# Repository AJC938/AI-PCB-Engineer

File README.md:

# AI-PCB-Engineer

An open-source electronics project delivering a protected sensor interface and peripheral power board for an **external ESP32 DevKit**.

> **Featured hardware:** Sensor Interface & Power Management Board for ESP32 · Rev A · V1.0.0
> CAD visualization only — **not fabricated or physically tested**.

## What is this PCB?

The board organizes power and signal connections between an ESP32 DevKit and compatible peripherals. It provides protected 5 V distribution, a regulated 3.3 V peripheral rail, conditioned sensor signals, and I²C, UART, and GPIO headers. The ESP32 is a separate development board and is powered through its own USB connection.

## Problem and solution

ESP32 GPIO uses 3.3 V logic and is not 5 V tolerant. Some 5 V ultrasonic modules can return a 5 V ECHO signal, which may exceed an ESP32 input's limits. Loose jumper-wire circuits also make power and signal wiring easier to get wrong.

This board provides a documented connector layout and dedicated signal conditioning: an SN74LVC1T45 translates ESP32 TRIG to the sensor's 5 V logic side, while an SN74LVC1G17 conditions ECHO for the ESP32. It also supplies protected 5 V and regulated 3.3 V peripheral power. Compatibility depends on the module's actual pinout and electrical characteristics; follow the [connector guide](docs/pinout/CONNECTION_GUIDE.md).

**Power regulation** creates a regulated supply rail. **Signal conditioning** adapts signal levels for compatible communication. They are separate circuits on this board.

## How it works

```mermaid
flowchart LR
  IN[5 V DC input] --> EF[TPS26600 eFuse] --> R5[Protected +5V_P]
  R5 --> LDO[TLV1117LV33] --> R3[+3V3_P peripheral rail]
  R5 --> USV[Ultrasonic VCC]
  ESP[External ESP32 DevKit<br/>powered separately by USB] --> IF[ESP32 signal interface]
  IF -->|TRIG, 3.3 V| TX[SN74LVC1T45]
  TX -->|TRIG, 5 V| US[Ultrasonic connector]
  US -->|ECHO, up to 5 V| RX[SN74LVC1G17]
  RX -->|conditioned ECHO| IF
  IF --> COM[I2C · UART · GPIO connectors]
  R3 -->|J5/J6; J4 via JP1| PER[Peripheral power]
  ESP ---|GND reference| US
```

`+3V3_P` powers peripherals. `3V3_ESP` is a separate ESP32 logic reference; the two rails are not connected together. See the [system architecture](docs/system-architecture/BOARD_ARCHITECTURE.md) and [electrical design](docs/electrical-design/ELECTRICAL_DESIGN.md).

## PCB gallery

Captured from the actual V1.0.0 project in KiCad applications. These are GUI screenshots, not command-line exports.

| Full schematic | PCB top layout |
|---|---|
|  |  |

| PCB bottom copper | 3D top view |
|---|---|
|  |  |

| 3D bottom view | Connector details |
|---|---|
|  |  |

[Power management schematic close-up](docs/visual-review/images/screenshots/02-power-management.png) · [All visual-review assets](docs/visual-review/VISUAL_REVIEW.md)

## Key specifications

| Item | Rev A specification |
|---|---|
| Board | 90 × 64 mm; 2 layers; FR-4; 1.6 mm; 1 oz copper |
| Component instances | 44 SMT + 8 THT = 52 |
| Input | Regulated 5 V DC, ±5%; ≥0.7 A recommended supply capacity |
| Peripheral rails | Protected +5V_P; regulated +3V3_P |
| 3.3 V peripheral load | 250 mA maximum, **calculated** at ambient ≤50 °C; not measured |
| Interfaces | ESP32 header, ultrasonic, I²C, UART, general-purpose GPIO |
| Primary protection | TPS26600 eFuse; current limit 0.51–0.69 A per release data |
| Validation | ERC 0; DRC 0 errors / 0 warnings; 0 unconnected; schematic parity 0 |

See [release notes](release/v1.0.0/RELEASE_NOTES_V1.0.0.md) and [digital validation evidence](docs/validation/DIGITAL_VALIDATION.md).

## Main components

- **TPS26600PWPR** — input eFuse with adjustable protection and current management.
- **TLV1117LV33** — regulates protected 5 V to the peripheral 3.3 V rail.
- **SN74LVC1T45** — translates ESP32 TRIG logic to the 5 V sensor side.
- **SN74LVC1G17** — conditions the ECHO input for the ESP32 logic domain.
- **J1–J6** — power input, ESP32, ultrasonic, UART, I²C, and GPIO connections.

[Complete BOM (CSV)](manufacturing/Sensor_Interface_Power_Board/RevA/assembly/Sensor_Interface_Power_Board_RevA_BOM.csv) · [Connector pinout](docs/pinout/CONNECTION_GUIDE.md)

## Downloads

| File | Download |
|---|---|
| KiCad project | [Project file](hardware/kicad/Sensor_Interface_Power_Board/Sensor_Interface_Power_Board.kicad_pro) · [Schematic](hardware/kicad/Sensor_Interface_Power_Board/Sensor_Interface_Power_Board.kicad_sch) · [PCB](hardware/kicad/Sensor_Interface_Power_Board/Sensor_Interface_Power_Board.kicad_pcb) |
| Complete manufacturing package | [ZIP](manufacturing/Sensor_Interface_Power_Board/RevA/packages/Sensor_Interface_PCB_RevA_Complete_Manufacturing.zip) |
| Fabrication package | [ZIP](manufacturing/Sensor_Interface_Power_Board/RevA/packages/Sensor_Interface_PCB_RevA_Fabrication.zip) |
| Assembly package | [ZIP](manufacturing/Sensor_Interface_Power_Board/RevA/packages/Sensor_Interface_PCB_RevA_Assembly.zip) |
| Copper Gerbers | [Top copper](manufacturing/Sensor_Interface_Power_Board/RevA/fabrication/Sensor_Interface_Power_Board-F_Cu.gtl) · [Bottom copper](manufacturing/Sensor_Interface_Power_Board/RevA/fabrication/Sensor_Interface_Power_Board-B_Cu.gbl) |
| Drill files | [Plated](manufacturing/Sensor_Interface_Power_Board/RevA/fabrication/Sensor_Interface_Power_Board-PTH.drl) · [Non-plated](manufacturing/Sensor_Interface_Power_Board/RevA/fabrication/Sensor_Interface_Power_Board-NPTH.drl) |
| Assembly data | [BOM](manufacturing/Sensor_Interface_Power_Board/RevA/assembly/Sensor_Interface_Power_Board_RevA_BOM.csv) · [CPL](manufacturing/Sensor_Interface_Power_Board/RevA/assembly/Sensor_Interface_Power_Board_RevA_CPL.csv) |
| 3D model | [STEP](manufacturing/Sensor_Interface_Power_Board/RevA/3d/Sensor_Interface_Power_Board_RevA.step) |
| Schematic | [PDF](manufacturing/Sensor_Interface_Power_Board/RevA/assembly/Sensor_Interface_Power_Board_RevA_schematic.pdf) |

## How to use

1. Supply the PCB with the specified regulated 5 V input.
2. Power the external ESP32 DevKit separately through its own USB connector.
3. Connect ESP32 signals using the documented interface and pinout.
4. Connect a compatible sensor using its documented connector labels and electrical requirements.
5. Follow the [power and safety requirements](docs/safety/SAFETY_AND_POWER.md), including sequencing rule R-31.

## Manufacturing

Download the [complete manufacturing ZIP](manufacturing/Sensor_Interface_Power_Board/RevA/packages/Sensor_Interface_PCB_RevA_Complete_Manufacturing.zip) or the separate fabrication and assembly packages. Ask a compatible supplier to confirm its capabilities, file requirements, and component sourcing before placing an order. The TPS26600PWPR stock status was uncertain at release; substitutions require written approval. See the [manufacturing guide](manufacturing/Sensor_Interface_Power_Board/RevA/fabrication/FABRICATION_NOTES.md) and [assembly requirements](docs/assembly/FULL_ASSEMBLY_REQUIREMENTS.md).

## Validation and limitations

**DIGITALLY VALIDATED — NOT FABRICATED OR PHYSICALLY TESTED.** ERC/DRC results are digital checks; no thermal, electrical, or functional measurements have been made.

- Reverse-polarity protection has a ground-loop limitation when other earthed equipment shares ground.
- Surge protection has not been demonstrated; do not infer a surge rating.
- The 3.3 V peripheral rail is limited to 250 mA calculated at ambient ≤50 °C.
- Follow power-sequencing rule R-31: power this board before or together with the ESP32.
- Sensor mating pin order has not been verified; check the module's own documentation.
- TPS26600PWPR availability was not confirmed on 2026-11-09.

Details: [physical validation status](docs/validation/PHYSICAL_VALIDATION_STATUS.md), [safety notes](docs/safety/SAFETY_AND_POWER.md), and [release notes](release/v1.0.0/RELEASE_NOTES_V1.0.0.md).

## License

Hardware design files and hardware documentation: [CERN-OHL-P-2.0](LICENSE-HARDWARE). Code: [MIT](LICENSE-CODE). Third-party material remains under its own terms; see [license scope](LICENSE_SCOPE.md) and [third-party notices](THIRD_PARTY_NOTICES.md).

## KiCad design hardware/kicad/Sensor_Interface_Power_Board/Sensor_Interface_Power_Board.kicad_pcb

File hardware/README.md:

# Hardware Sources

| Path | Contents |
|---|---|
| [`kicad/Sensor_Interface_Power_Board/`](kicad/Sensor_Interface_Power_Board/) | The board: `.kicad_pro`, `.kicad_sch`, `.kicad_pcb`, `fp-lib-table`, project footprint library `Sensor_Interface_Power_Board.pretty/` (U5, TI PWP0016A) |
| `kicad/Sensor_Interface_Power_Board/build/` | Scripts that generated and verified the design (schematic generator, placement plan, router, silkscreen, verifiers, BOM builder) |
| `libraries/` | Reserved for shared project libraries (currently empty; the only custom footprint lives with the project) |
| `sandbox/` | Throwaway MCP experiments (gitignored) |

**Requirements to open:** KiCad 10.0.x with its standard libraries. No absolute paths are used. Custom symbols:
none (all symbols are embedded in the schematic). Custom 3D models: none (U5 uses the KiCad HTSSOP-16 model).

The KiCad project folder stays at `hardware/kicad/` (rather than being moved) so that the build scripts, report
links and git history remain valid.

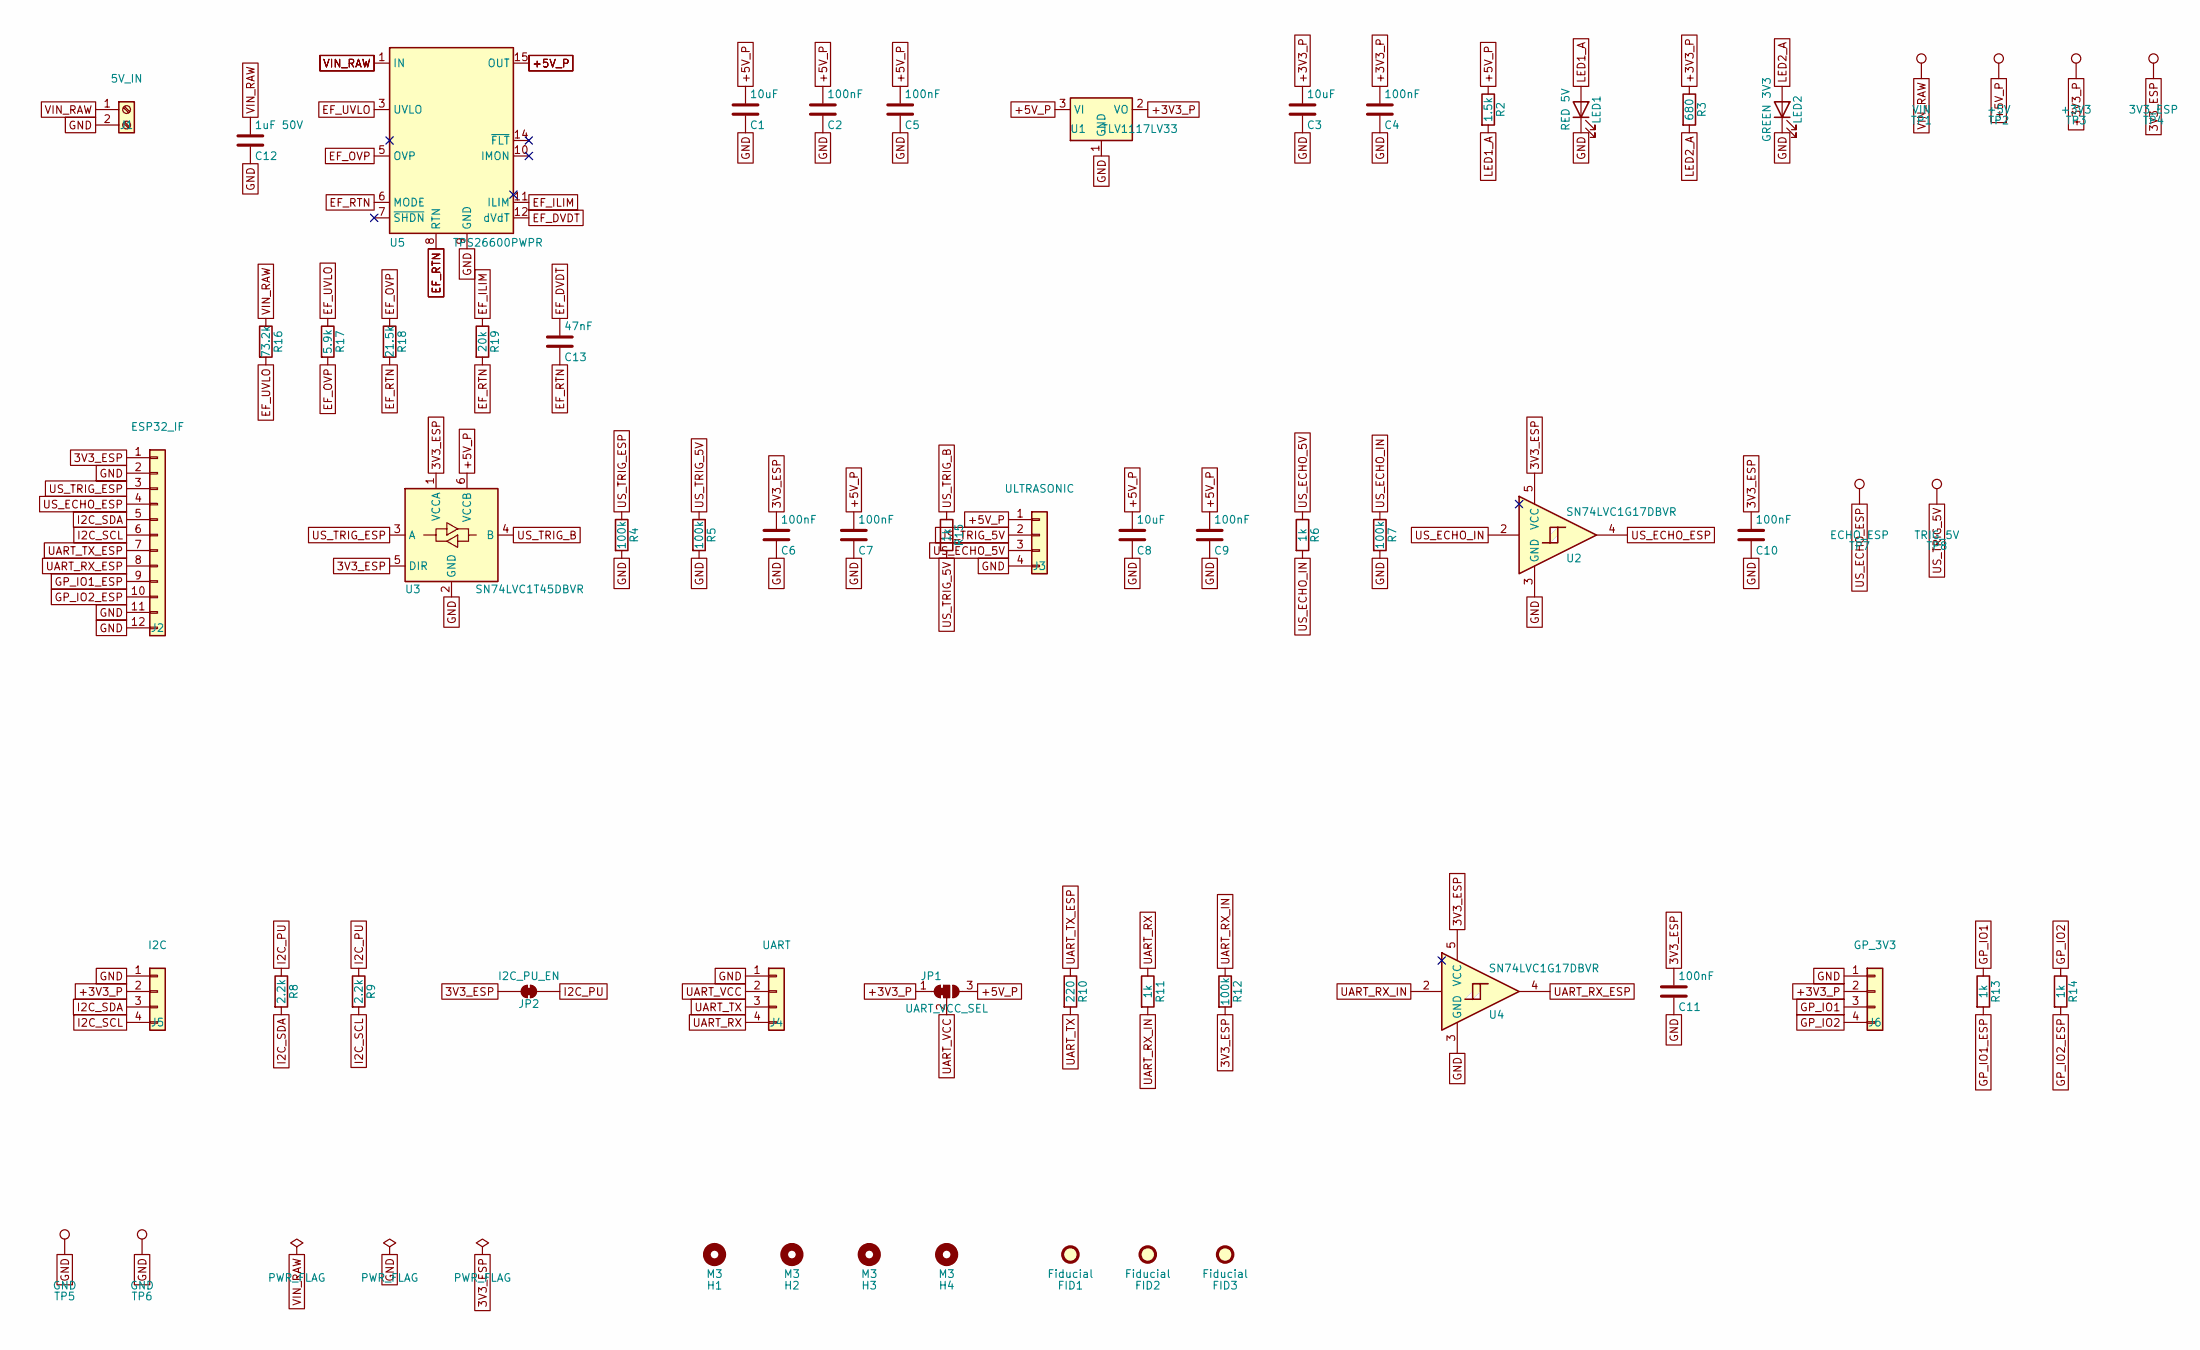
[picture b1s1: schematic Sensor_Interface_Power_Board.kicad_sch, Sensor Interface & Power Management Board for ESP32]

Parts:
C1, C3, C8: 10uF; C_0603_1608Metric; MPN CL10A106KP8NNNC
C2, C4, C5, C6, C7, C9, C10, C11: 100nF; C_0603_1608Metric; MPN GRM188R71C104KA01D
C12: 1uF 50V; C_0603_1608Metric; MPN CL10A105KB8NNNC
C13: 47nF; C_0603_1608Metric; MPN CL10B473KB8NNNC
FID1, FID2, FID3: Fiducial; Fiducial_1mm_Mask2mm
H1, H2, H3, H4: M3; MountingHole_3.2mm_M3
J1: 5V_IN; TerminalBlock_Phoenix_MKDS-1,5-2-5.08_1x02_P5.08mm_Horizont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; MPN 1715721
J2: ESP32_IF; PinHeader_1x12_P2.54mm_Vertical; MPN HTSW-112-07-T-S
J3: ULTRASONIC; PinHeader_1x04_P2.54mm_Vertical; MPN HTSW-104-07-T-S
J4: UART; PinHeader_1x04_P2.54mm_Vertical; MPN HTSW-104-07-T-S
J5: I2C; PinHeader_1x04_P2.54mm_Vertical; MPN HTSW-104-07-T-S
J6: GP_3V3; PinHeader_1x04_P2.54mm_Vertical; MPN HTSW-104-07-T-S
JP1: UART_VCC_SEL; SolderJumper-3_P1.3mm_Bridged12_RoundedPad1.0x1.5mm
JP2: I2C_PU_EN; SolderJumper-2_P1.3mm_Bridged_RoundedPad1.0x1.5mm
LED1: RED 5V; LED_D5.0mm; MPN WP7113ID
LED2: GREEN 3V3; LED_D5.0mm; MPN WP7113SGD
R2: 1.5k; R_0603_1608Metric; MPN ERJ-3EKF1501V
R3: 680; R_0603_1608Metric; MPN ERJ-3EKF6800V
R4, R5, R7, R12: 100k; R_0603_1608Metric; MPN ERJ-3EKF1003V
R6, R11, R13, R14, R15: 1k; R_0603_1608Metric; MPN ERJ-3EKF1001V
R8, R9: 2.2k; R_0603_1608Metric; MPN ERJ-3EKF2201V
R10: 220; R_0603_1608Metric; MPN ERJ-3EKF2200V
R16: 73.2k; R_0603_1608Metric; MPN ERJ-3EKF7322V
R17: 5.9k; R_0603_1608Metric; MPN ERJ-3EKF5901V
R18: 21.5k; R_0603_1608Metric; MPN ERJ-3EKF2152V
R19: 20k; R_0603_1608Metric; MPN ERJ-3EKF2002V
TP1: VIN; TestPoint_Keystone_5015_Micro_Mini; MPN 5015
TP2: +5V; TestPoint_Keystone_5015_Micro_Mini; MPN 5015
TP3: +3V3; TestPoint_Keystone_5015_Micro_Mini; MPN 5015
TP4: 3V3_ESP; TestPoint_Keystone_5015_Micro_Mini; MPN 5015
TP5, TP6: GND; TestPoint_Keystone_5015_Micro_Mini; MPN 5015
TP7: ECHO_ESP; TestPoint_Keystone_5015_Micro_Mini; MPN 5015
TP8: TRIG_5V; TestPoint_Keystone_5015_Micro_Mini; MPN 5015
U1: TLV1117LV33; SOT-223-3_TabPin2; MPN TLV1117LV33DCYR
U2, U4: SN74LVC1G17DBVR; SOT-23-5; MPN SN74LVC1G17DBVR
U3: SN74LVC1T45DBVR; SOT-23-6; MPN SN74LVC1T45DBVR
U5: TPS26600PWPR; TI_PWP0016A_HTSSOP-16-1EP_4.4x5mm_P0.65mm_EP3.4x5mm; MPN TPS26600PWPR

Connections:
3V3_ESP: C6.1, C10.1, C11.1, J2.1, JP2.1 (A), R12.2, TP4.1, U2.5 (VCC), U3.1 (VCCA), U3.5 (DIR), U4.5 (VCC)
+3V3_P: C3.1, C4.1, J5.2, J6.2, JP1.1 (A), R3.1, TP3.1, U1.2 (VO)
+5V_P: C1.1, C2.1, C5.1, C7.1, C8.1, C9.1, J3.1, JP1.3 (B), R2.1, TP2.1, U1.3 (VI), U3.6 (VCCB), U5.15 (OUT), U5.16 (OUT)
EF_DVDT: C13.1, U5.12 (dVdT)
EF_ILIM: R19.1, U5.11 (ILIM)
EF_OVP: R17.2, R18.1, U5.5 (OVP)
EF_RTN: C13.2, R18.2, R19.2, U5.6 (MODE), U5.8 (RTN), U5.17 (RTN)
EF_UVLO: R16.2, R17.1, U5.3 (UVLO)
GND: C1.2, C2.2, C3.2, C4.2, C5.2, C6.2, C7.2, C8.2, C9.2, C10.2, C11.2, C12.2, J1.2, J2.2, J2.11, J2.12, J3.4, J4.1, J5.1, J6.1, LED1.1 (K), LED2.1 (K), R4.2, R5.2, R7.2, TP5.1, TP6.1, U1.1 (GND), U2.3 (GND), U3.2 (GND), U4.3 (GND), U5.9 (GND)
GP_IO1: J6.3, R13.1
GP_IO1_ESP: J2.9, R13.2
GP_IO2: J6.4, R14.1
GP_IO2_ESP: J2.10, R14.2
I2C_PU: JP2.2 (B), R8.1, R9.1
I2C_SCL: J2.6, J5.4, R9.2
I2C_SDA: J2.5, J5.3, R8.2
LED1_A: LED1.2 (A), R2.2
LED2_A: LED2.2 (A), R3.2
UART_RX: J4.4, R11.1
UART_RX_ESP: J2.8, U4.4
UART_RX_IN: R11.2, R12.1, U4.2
UART_TX: J4.3, R10.2
UART_TX_ESP: J2.7, R10.1
UART_VCC: J4.2, JP1.2 (C)
US_ECHO_5V: J3.3, R6.1
US_ECHO_ESP: J2.4, TP7.1, U2.4
US_ECHO_IN: R6.2, R7.1, U2.2
US_TRIG_5V: J3.2, R5.1, R15.2, TP8.1
US_TRIG_B: R15.1, U3.4 (B)
US_TRIG_ESP: J2.3, R4.1, U3.3 (A)
VIN_RAW: C12.1, J1.1, R16.1, TP1.1, U5.1 (IN), U5.2 (IN)

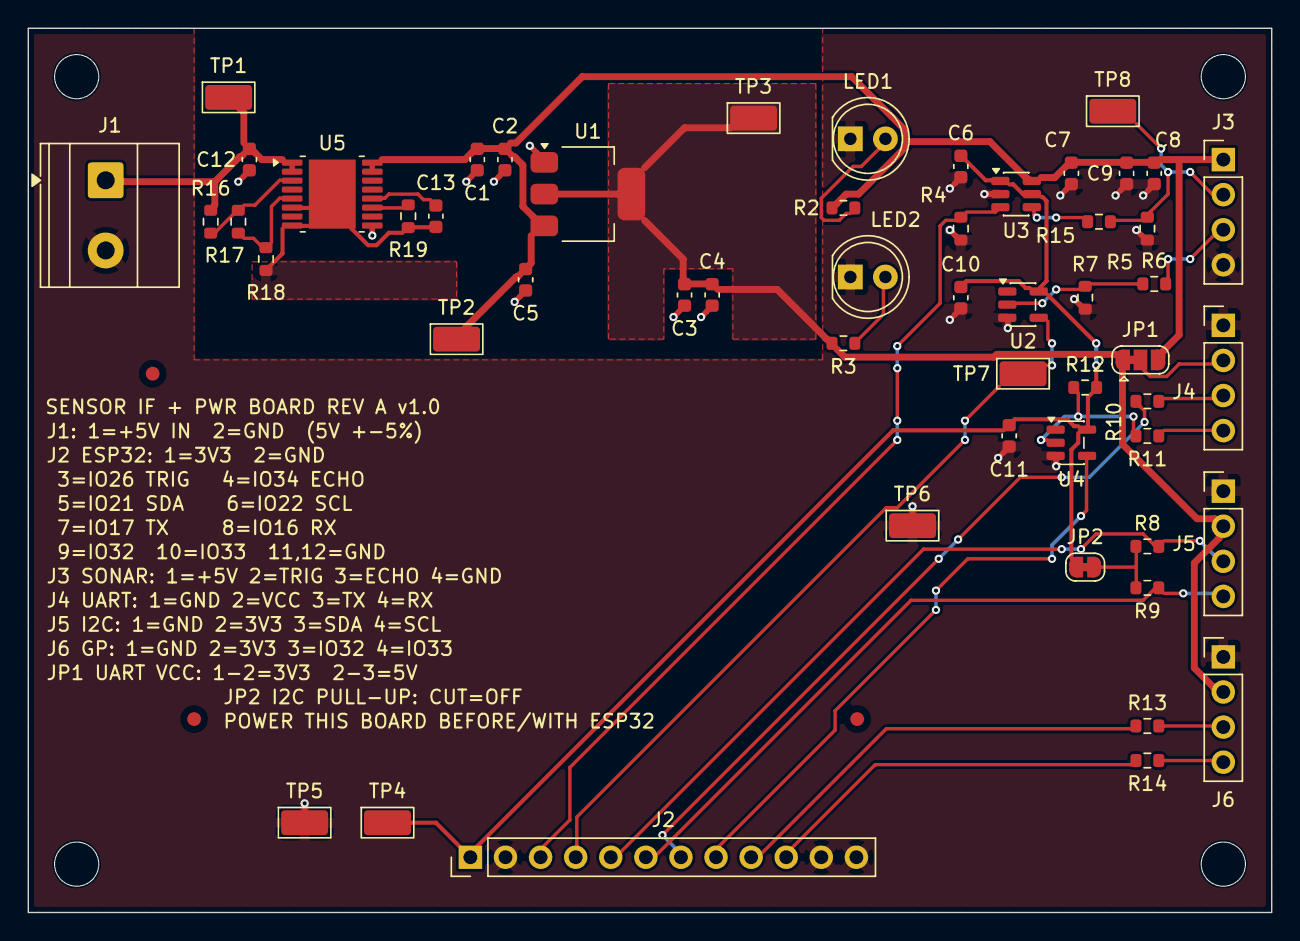
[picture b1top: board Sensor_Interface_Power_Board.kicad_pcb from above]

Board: 2 copper layers, 90.0 x 64.0 mm, 61 parts (0 on the bottom side), 31 nets.

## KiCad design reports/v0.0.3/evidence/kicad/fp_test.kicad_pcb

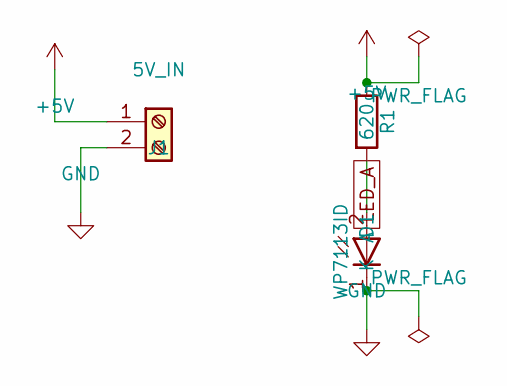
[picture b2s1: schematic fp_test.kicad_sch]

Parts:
D1: WP7113ID; LED_D5.0mm_WP7113ID; MPN WP7113ID
J1: 5V_IN; TerminalBlock_Phoenix_MKDS-1,5-2-5.08_1x02_P5.08mm_Horizont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; MPN 1715721
R1: 620; R_Axial_DIN0207_L6.3mm_D2.5mm_P10.16mm_Horizontal; MPN MFR-25FBF52-620R

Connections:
+5V: J1.1, R1.1
GND: D1.1 (K), J1.2
LED_A: D1.2 (A), R1.2

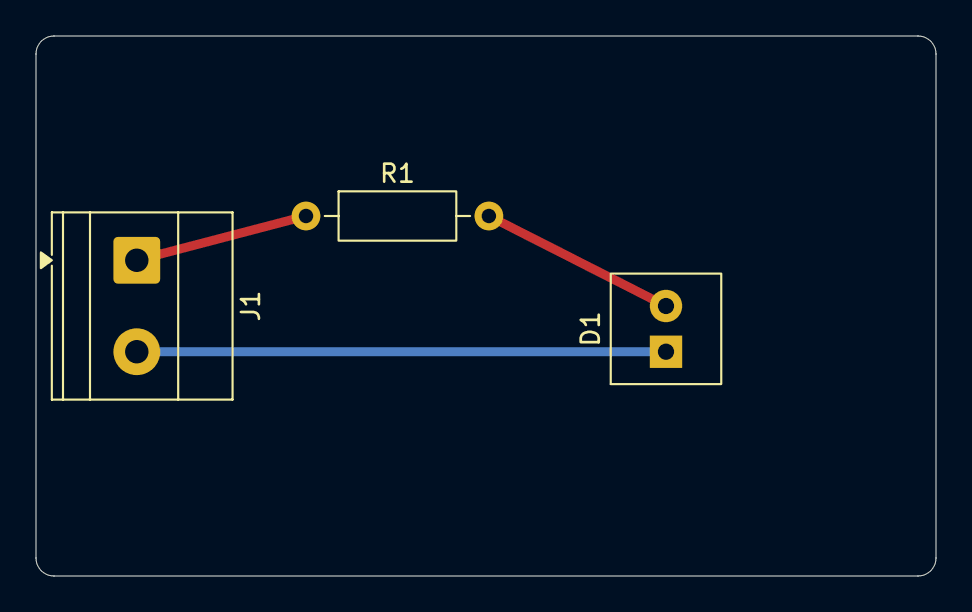
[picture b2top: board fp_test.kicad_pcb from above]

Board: 2 copper layers, 50.0 x 30.0 mm, 3 parts (0 on the bottom side), 3 nets.
